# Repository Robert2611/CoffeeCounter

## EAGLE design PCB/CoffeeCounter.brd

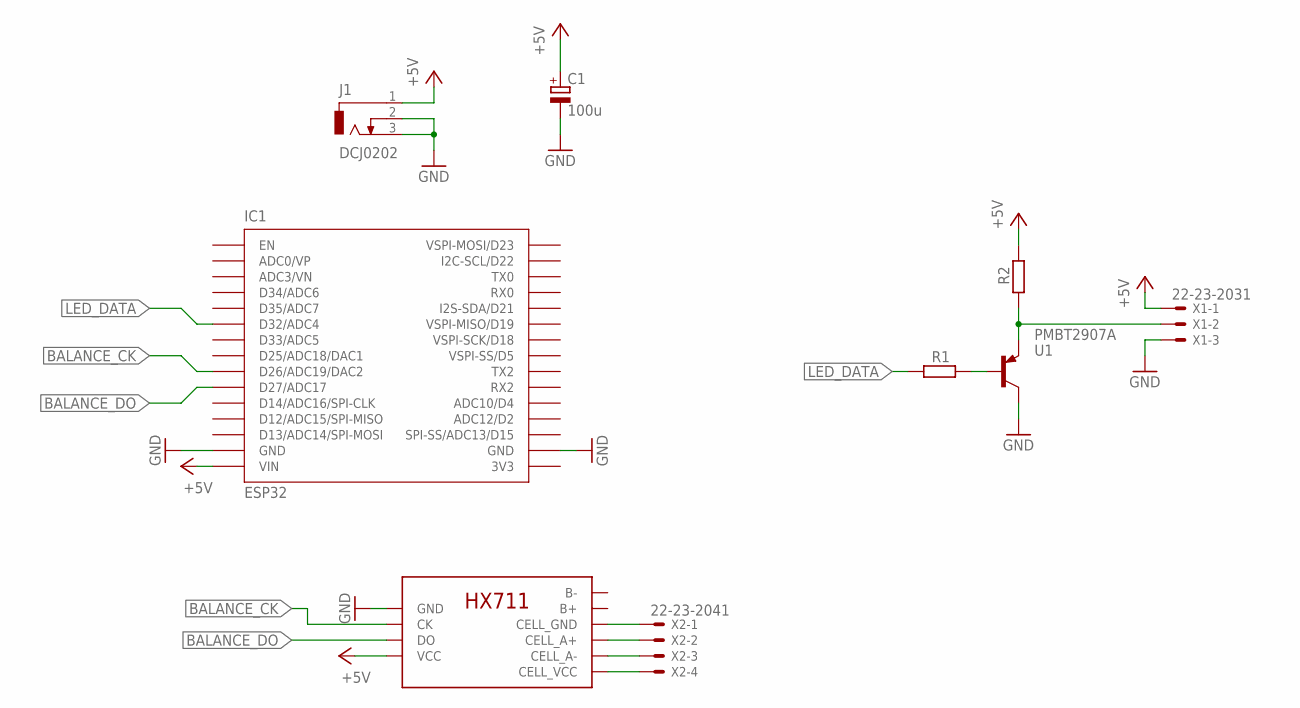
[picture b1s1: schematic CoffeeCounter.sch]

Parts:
C1: 100u; E3,5-8
IC1: ESP32
J1: DCJ0202
R1, R2: R-EU_R0603; R0603
U1: PMBT2907A; SOT23_NEX
U$1: HX711_BREAKOUT
X1: 22-23-2031
X2: 22-23-2041

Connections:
3V3: IC1.3V3
+5V: C1.+, IC1.VIN, J1.1, R2.2, U$1.VCC, X1.1
ADC3/VN: IC1.VN (ADC3/VN)
BALANCE_CK: IC1.D26 (D26/ADC19/DAC2), U$1.CK
BALANCE_DO: IC1.D27 (D27/ADC17), U$1.DO
D13/ADC14/SPI-MOSI: IC1.D13 (D13/ADC14/SPI-MOSI)
GND: C1.-, IC1.GND@1 (GND), IC1.GND@2 (GND), J1.2, J1.3, U1.3 (C), U$1.GND, X1.3
LED_DATA: IC1.D32 (D32/ADC4), R1.1
unnamed: R1.2, U1.1 (B)
unnamed: R2.1, U1.2 (E), X1.2
unnamed: U$1.CELL_GND, X2.1
unnamed: U$1.CELL_A+, X2.2
unnamed: U$1.CELL_A-, X2.3
unnamed: U$1.CELL_OUT+ (CELL_VCC), X2.4

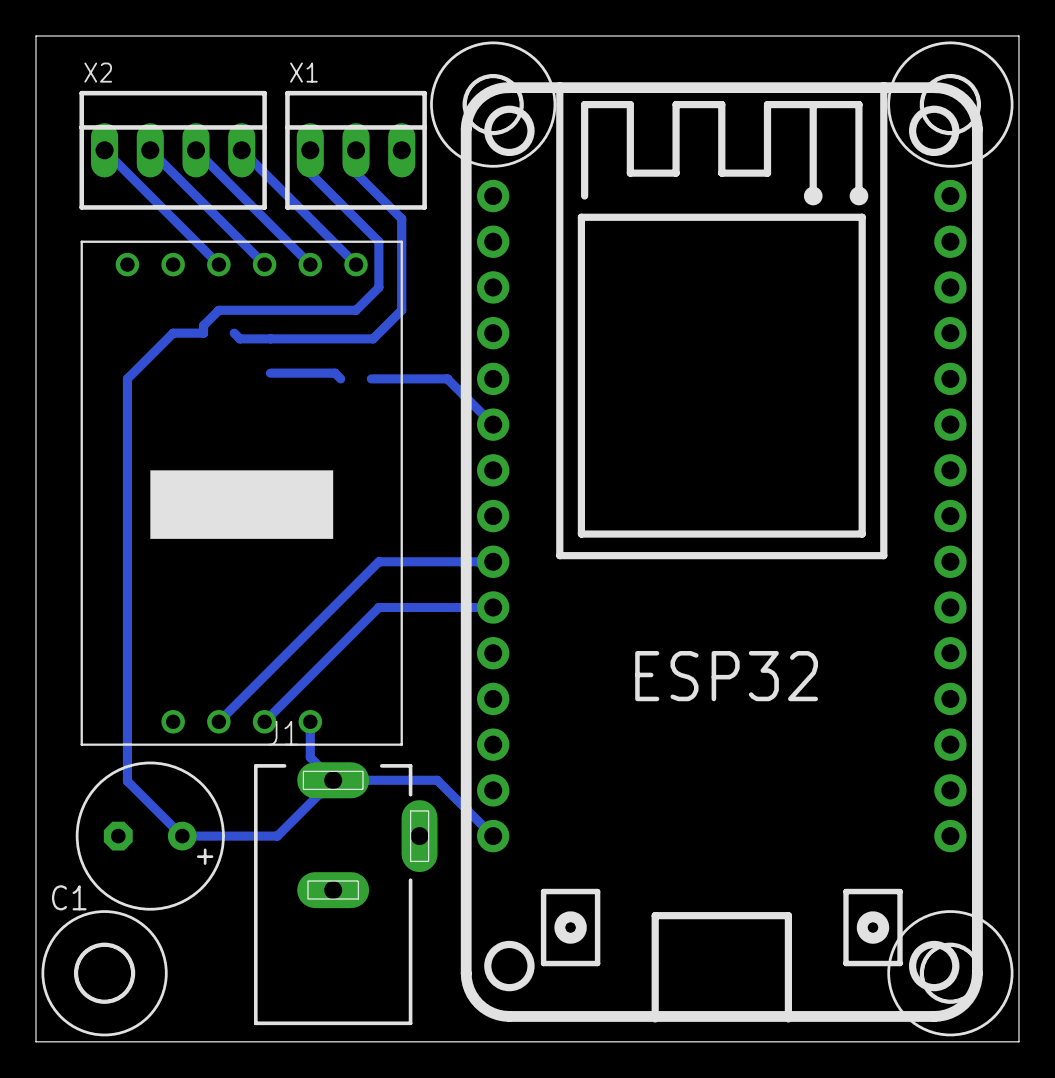
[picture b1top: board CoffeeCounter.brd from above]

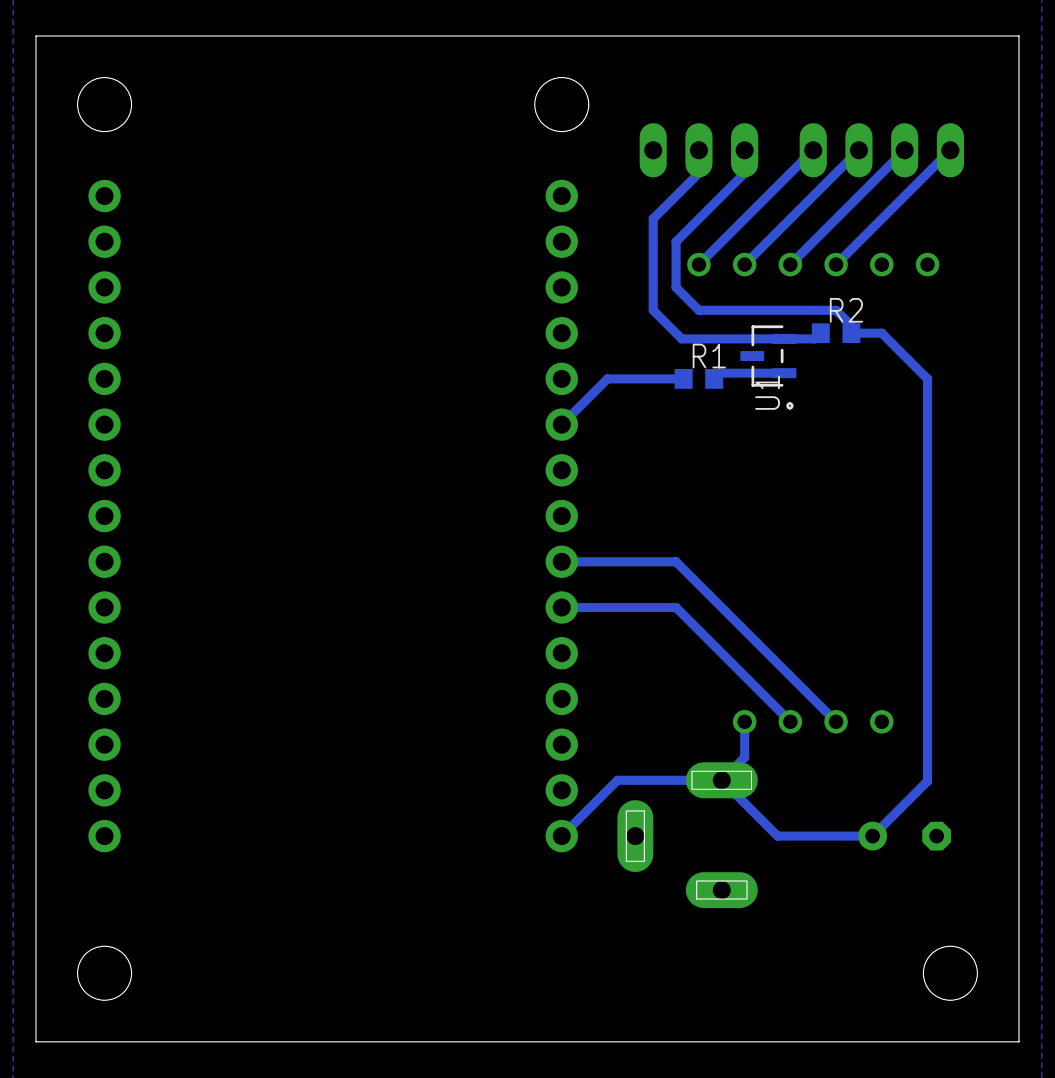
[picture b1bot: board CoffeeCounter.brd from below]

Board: 2 copper layers, 54.6 x 55.9 mm, 13 parts (3 on the bottom side), 11 nets.

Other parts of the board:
U$2, U$3, U$4, U$5: LOCH_M3

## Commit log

2020-11-16 PCB data added
2020-11-16 UI with ESPUI
2020-11-18 Weight dependent LED added
2020-11-20 LED mode "separated" added
2020-11-20 CAD files added
2021-01-24 Captive portal added
2021-01-24 - Wifi moved to separate core - Wifi password added
2021-01-24 LED animation for pumping added
2021-01-25 Last measures weights in history

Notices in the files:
parts and their libraries:
COPYRIGHT: Copyright (C) 2016 Accelerated Designs. All rights reserved
